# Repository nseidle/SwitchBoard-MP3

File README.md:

Switchboard MP3 Player
=======

This project documents the modifications made to a vintage phone switchboard. This is an interactive exhibit at the WOW children's museum in Lafayette. Any of the audio plugs can be inserted into any of the ports in the top console. The light will turn on and one of 74 MP3s will play out the corded phone.

It was awesome to work on.

I appreciate the switchboard contained its own solder. From 1956!

Above, shows all the original glass lamp covers

[Movie of LEDs](Images/Switchboard%20LEDs.mp4)

Repository Contents
-------------------

* **/firmware** - The code that runs on the ESP32.
* **/hardware** - A custom I/O board capable of 40 inputs and 40 outputs per board, with the ability to chain any number of boards together.

License Information
-------------------

This design is [OSHW](http://www.oshwa.org/definition/) and public domain but you buy me a beer if you use this and we meet someday ([Beerware license](http://en.wikipedia.org/wiki/Beerware)).

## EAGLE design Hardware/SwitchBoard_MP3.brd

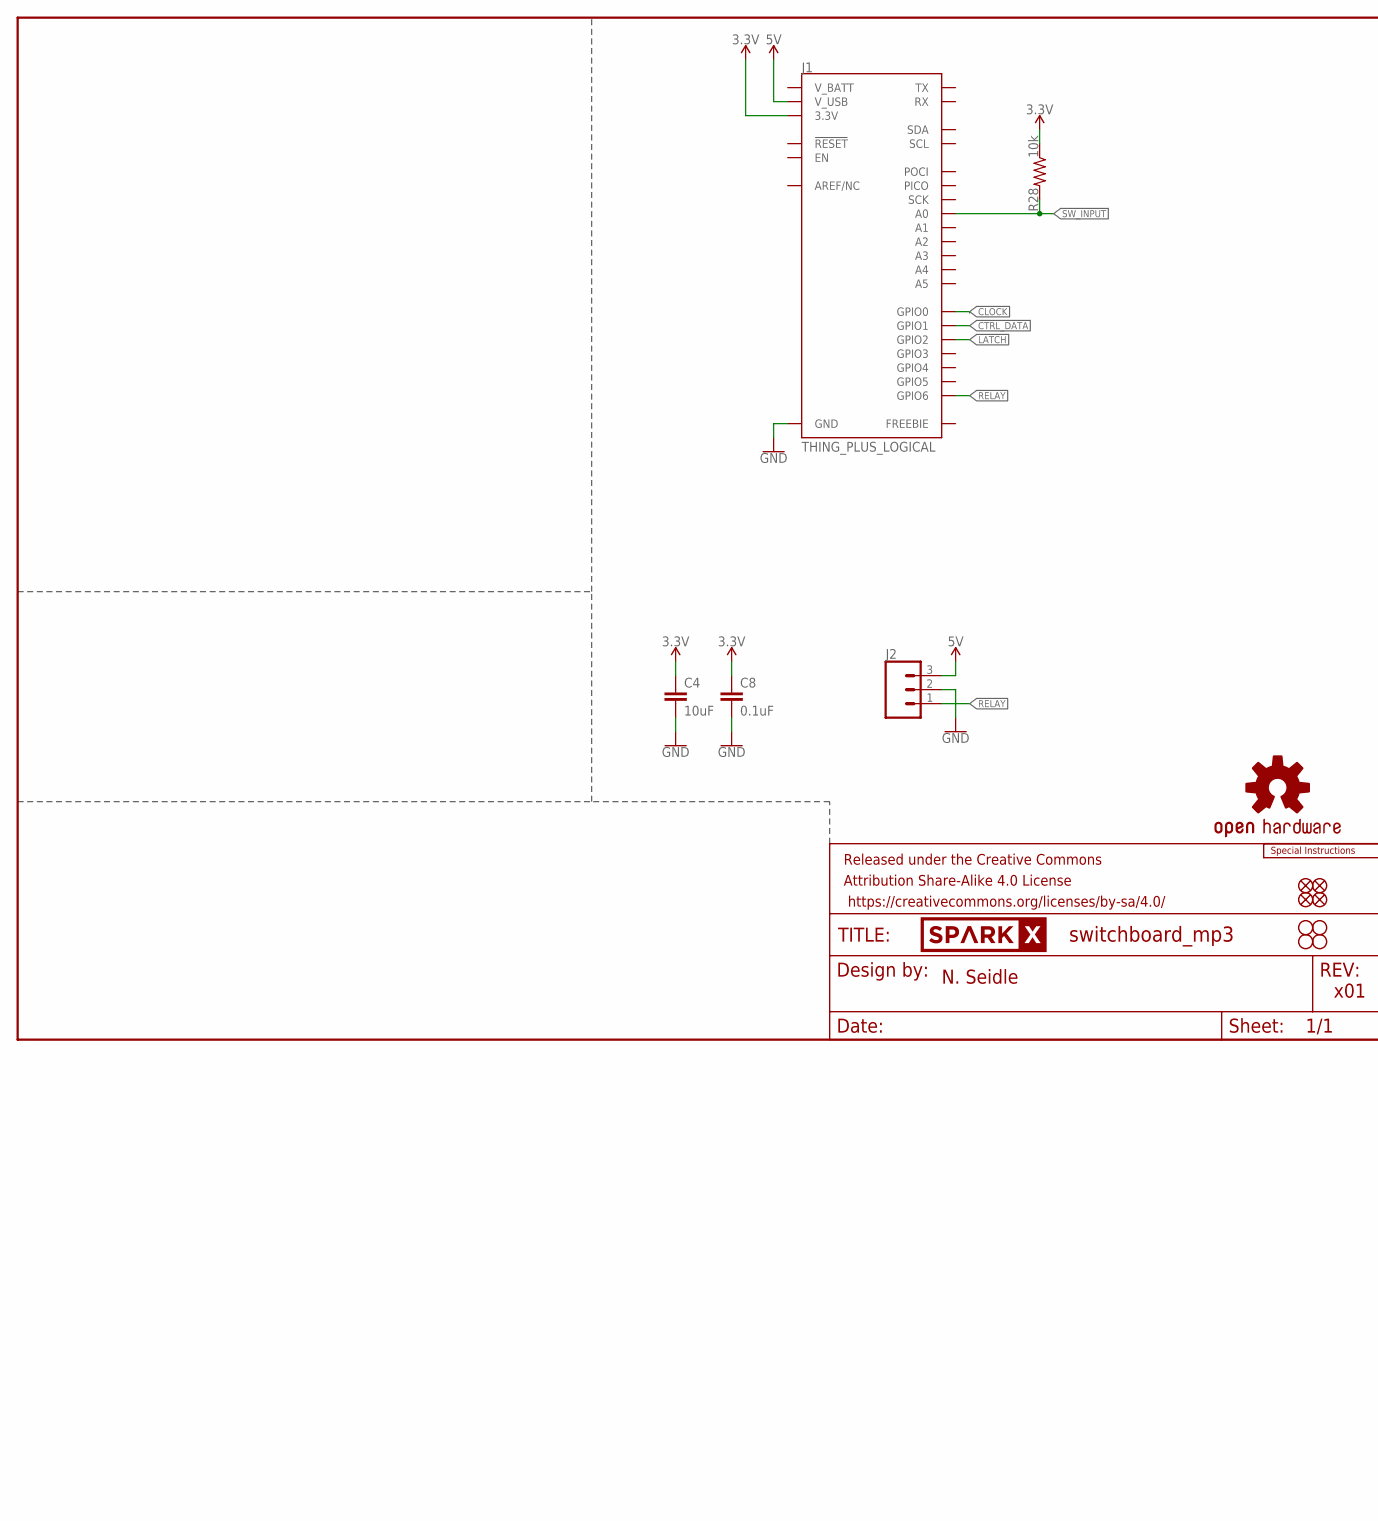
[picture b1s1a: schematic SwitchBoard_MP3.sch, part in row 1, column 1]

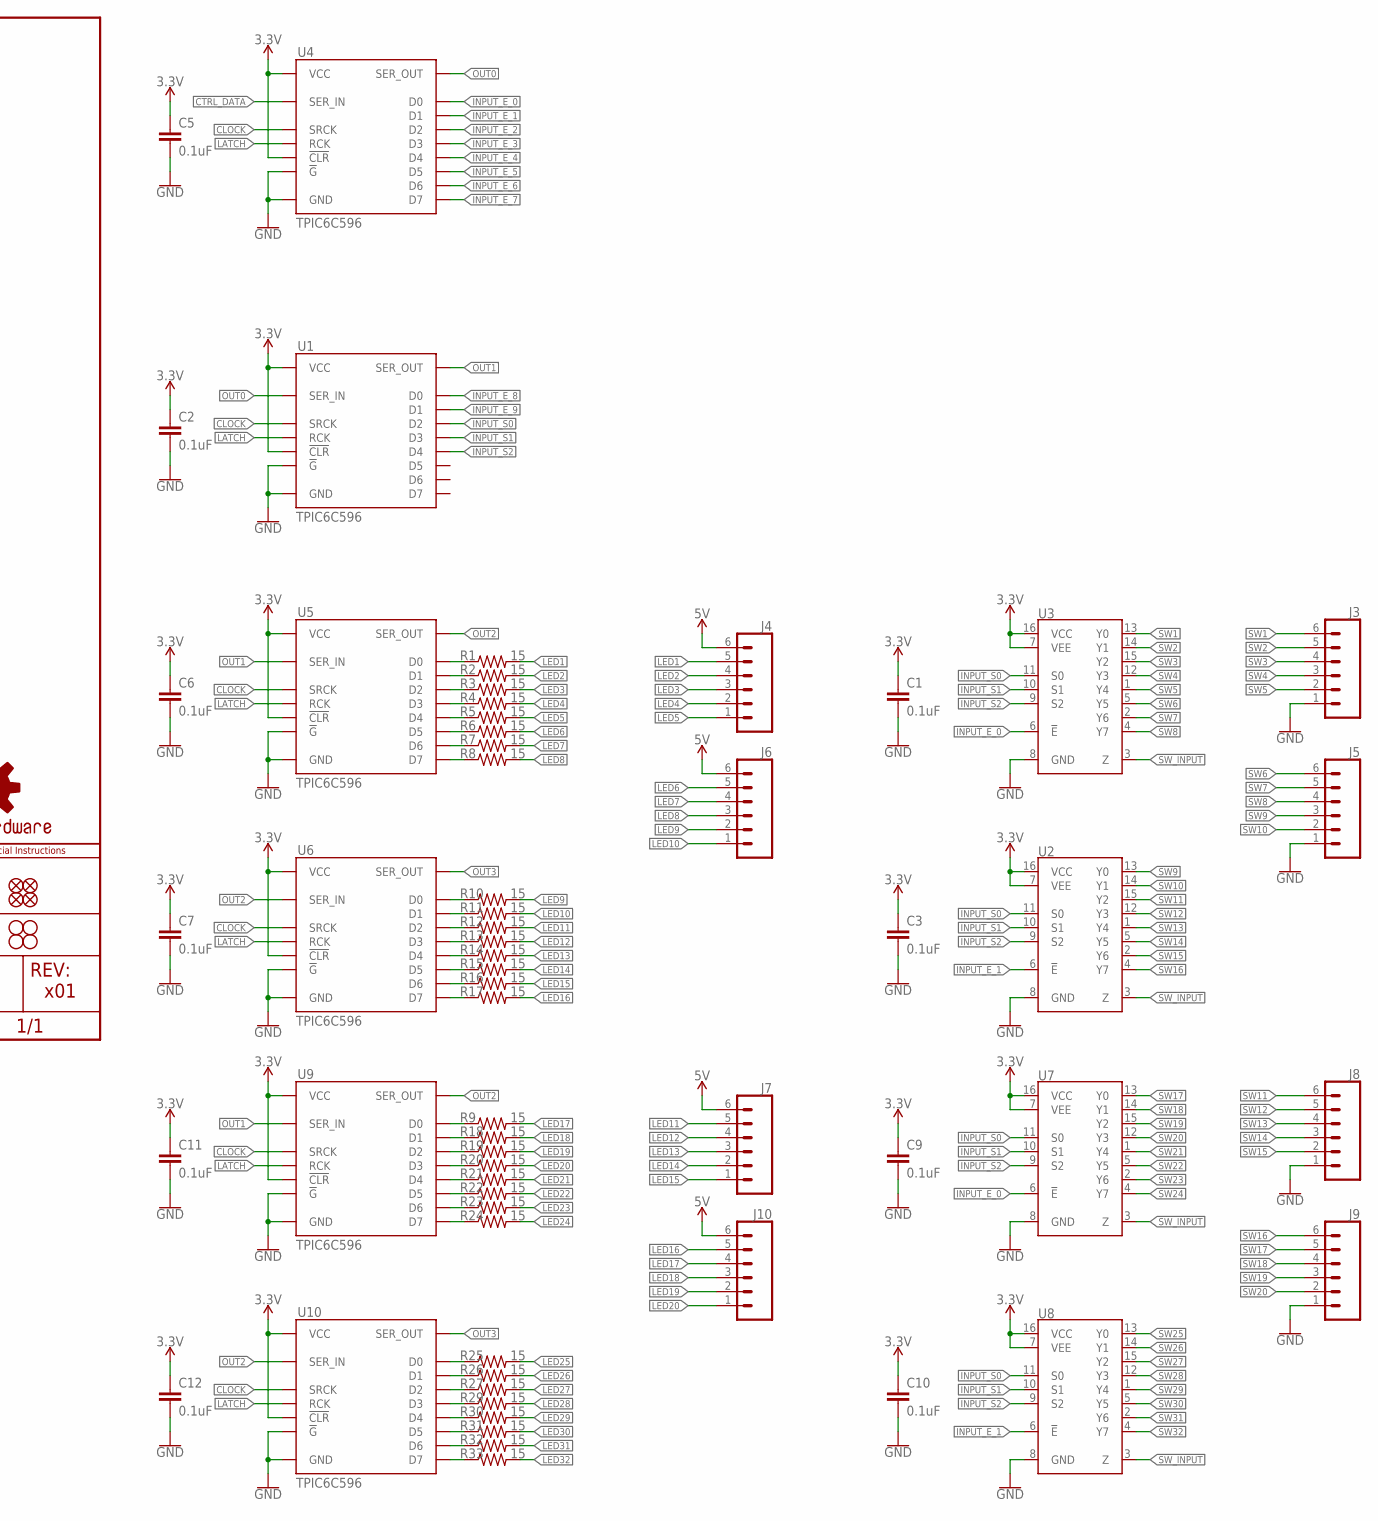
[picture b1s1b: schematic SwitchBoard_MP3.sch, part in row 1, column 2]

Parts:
C1, C2, C3, C5, C6, C7, C8, C9, C10, C11, C12: 0.1uF; 0603
C4: 10uF; 0805
FD1, FD2, FD3, FD4: FIDUCIAL1X2; FIDUCIAL-1X2
FRAME1: FRAME-LETTER; CREATIVE_COMMONS
H1, H2, H3, H4: STAND-OFF
J1: THING_PLUS_LOGICAL; THING_PLUS
J2: CONN_03JST-PTH-NS; JST-3-PTH-NS
J3, J4, J5, J6, J7, J8, J9, J10: CONN_06JST-SMD-LOCKING; JST-6-SMD-1.25MM-LOCKING
LOGO1: SPECIAL_INSTRUCTIONS-ORDERING; ORDERING_INSTRUCTIONS
LOGO2: OSHW-LOGOS; OSHW-LOGO-S
R1, R2, R3, R4, R5, R6, R7, R8, R9, R10, R11, R12, R13, R14, R15, R16, R17, R18, R19, R20, R21, R22, R23, R24, R25, R26, R27, R29, R30, R31, R32, R33: 15; 0603
R28: 10k; 0603
U1, U4, U5, U6, U9, U10: TPIC6C596; SO016
U2, U3, U7, U8: 744051; SO16
U$1: SPARKX-LOGO4; SPARKX-MEDIUM

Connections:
3.3V: C1.1, C2.1, C3.1, C4.1, C5.1, C6.1, C7.1, C8.1, C9.1, C10.1, C11.1, C12.1, J1.27 (3.3V), R28.1, U1.1 (VCC), U1.7 (!CLR), U2.7 (VEE), U2.16 (VCC), U3.7 (VEE), U3.16 (VCC), U4.1 (VCC), U4.7 (!CLR), U5.1 (VCC), U5.7 (!CLR), U6.1 (VCC), U6.7 (!CLR), U7.7 (VEE), U7.16 (VCC), U8.7 (VEE), U8.16 (VCC), U9.1 (VCC), U9.7 (!CLR), U10.1 (VCC), U10.7 (!CLR)
5V: J1.10 (V_USB), J2.3, J4.6, J6.6, J7.6, J10.6
CLOCK: J1.9 (GPIO0), U1.15 (SRCK), U4.15 (SRCK), U5.15 (SRCK), U6.15 (SRCK), U9.15 (SRCK), U10.15 (SRCK)
CTRL_DATA: J1.8 (GPIO1), U4.2 (SER_IN)
GND: C1.2, C2.2, C3.2, C4.2, C5.2, C6.2, C7.2, C8.2, C9.2, C10.2, C11.2, C12.2, J1.25 (GND), J2.2, J3.1, J5.1, J8.1, J9.1, U1.8 (!G), U1.16 (GND), U2.8 (GND), U3.8 (GND), U4.8 (!G), U4.16 (GND), U5.8 (!G), U5.16 (GND), U6.8 (!G), U6.16 (GND), U7.8 (GND), U8.8 (GND), U9.8 (!G), U9.16 (GND), U10.8 (!G), U10.16 (GND)
INPUT_!E!_0: U3.6 (!E!), U4.3 (D0), U7.6 (!E!)
INPUT_!E!_1: U2.6 (!E!), U4.4 (D1), U8.6 (!E!)
INPUT_!E!_2: U4.5 (D2)
INPUT_!E!_3: U4.6 (D3)
INPUT_!E!_4: U4.11 (D4)
INPUT_!E!_5: U4.12 (D5)
INPUT_!E!_6: U4.13 (D6)
INPUT_!E!_7: U4.14 (D7)
INPUT_!E!_8: U1.3 (D0)
INPUT_!E!_9: U1.4 (D1)
INPUT_S0: U1.5 (D2), U2.11 (S0), U3.11 (S0), U7.11 (S0), U8.11 (S0)
INPUT_S1: U1.6 (D3), U2.10 (S1), U3.10 (S1), U7.10 (S1), U8.10 (S1)
INPUT_S2: U1.11 (D4), U2.9 (S2), U3.9 (S2), U7.9 (S2), U8.9 (S2)
LATCH: J1.7 (GPIO2), U1.10 (RCK), U4.10 (RCK), U5.10 (RCK), U6.10 (RCK), U9.10 (RCK), U10.10 (RCK)
LED1: J4.5, R1.2
LED2: J4.4, R2.2
LED3: J4.3, R3.2
LED4: J4.2, R4.2
LED5: J4.1, R5.2
LED6: J6.5, R6.2
LED7: J6.4, R7.2
LED8: J6.3, R8.2
LED9: J6.2, R10.2
LED10: J6.1, R11.2
LED11: J7.5, R12.2
LED12: J7.4, R13.2
LED13: J7.3, R14.2
LED14: J7.2, R15.2
LED15: J7.1, R16.2
LED16: J10.5, R17.2
LED17: J10.4, R9.2
LED18: J10.3, R18.2
LED19: J10.2, R19.2
LED20: J10.1, R20.2
LED21: R21.2
LED22: R22.2
LED23: R23.2
LED24: R24.2
LED25: R25.2
LED26: R26.2
LED27: R27.2
LED28: R29.2
LED29: R30.2
LED30: R31.2
LED31: R32.2
LED32: R33.2
unnamed: R1.1, U5.3 (D0)
unnamed: R2.1, U5.4 (D1)
unnamed: R3.1, U5.5 (D2)
unnamed: R4.1, U5.6 (D3)
unnamed: R5.1, U5.11 (D4)
unnamed: R6.1, U5.12 (D5)
unnamed: R7.1, U5.13 (D6)
unnamed: R8.1, U5.14 (D7)
unnamed: R9.1, U9.3 (D0)
unnamed: R10.1, U6.3 (D0)
unnamed: R11.1, U6.4 (D1)
unnamed: R12.1, U6.5 (D2)
unnamed: R13.1, U6.6 (D3)
unnamed: R14.1, U6.11 (D4)
unnamed: R15.1, U6.12 (D5)
unnamed: R16.1, U6.13 (D6)
unnamed: R17.1, U6.14 (D7)
unnamed: R18.1, U9.4 (D1)
unnamed: R19.1, U9.5 (D2)
unnamed: R20.1, U9.6 (D3)
unnamed: R21.1, U9.11 (D4)
unnamed: R22.1, U9.12 (D5)
unnamed: R23.1, U9.13 (D6)
unnamed: R24.1, U9.14 (D7)
unnamed: R25.1, U10.3 (D0)
unnamed: R26.1, U10.4 (D1)
unnamed: R27.1, U10.5 (D2)
unnamed: R29.1, U10.6 (D3)
unnamed: R30.1, U10.11 (D4)
unnamed: R31.1, U10.12 (D5)
unnamed: R32.1, U10.13 (D6)
unnamed: R33.1, U10.14 (D7)
OUT0: U1.2 (SER_IN), U4.9 (SER_OUT)
OUT1: U1.9 (SER_OUT), U5.2 (SER_IN), U9.2 (SER_IN)
OUT2: U5.9 (SER_OUT), U6.2 (SER_IN), U9.9 (SER_OUT), U10.2 (SER_IN)
OUT3: U6.9 (SER_OUT), U10.9 (SER_OUT)
RELAY: J1.3 (GPIO6), J2.1
SW1: J3.6, U3.13 (Y0)
SW2: J3.5, U3.14 (Y1)
SW3: J3.4, U3.15 (Y2)
SW4: J3.3, U3.12 (Y3)
SW5: J3.2, U3.1 (Y4)
SW6: J5.6, U3.5 (Y5)
SW7: J5.5, U3.2 (Y6)
SW8: J5.4, U3.4 (Y7)
SW9: J5.3, U2.13 (Y0)
SW10: J5.2, U2.14 (Y1)
SW11: J8.6, U2.15 (Y2)
SW12: J8.5, U2.12 (Y3)
SW13: J8.4, U2.1 (Y4)
SW14: J8.3, U2.5 (Y5)
SW15: J8.2, U2.2 (Y6)
SW16: J9.6, U2.4 (Y7)
SW17: J9.5, U7.13 (Y0)
SW18: J9.4, U7.14 (Y1)
SW19: J9.3, U7.15 (Y2)
SW20: J9.2, U7.12 (Y3)
SW21: U7.1 (Y4)
SW22: U7.5 (Y5)
SW23: U7.2 (Y6)
SW24: U7.4 (Y7)
SW25: U8.13 (Y0)
SW26: U8.14 (Y1)
SW27: U8.15 (Y2)
SW28: U8.12 (Y3)
SW29: U8.1 (Y4)
SW30: U8.5 (Y5)
SW31: U8.2 (Y6)
SW32: U8.4 (Y7)
SW_INPUT: J1.24 (A0), R28.2, U2.3 (Z), U3.3 (Z), U7.3 (Z), U8.3 (Z)

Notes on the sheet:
x01
N. Seidle

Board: 4 copper layers, 88 parts (2 on the bottom side), 89 nets, no tracks yet.

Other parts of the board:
U$2: 5_4_3_2_1_V0
U$3, U$7, U$11, U$12: LAMP0
U$4, U$6, U$8, U$9, U$10: SWITCH0
U$5: G_5_4_3_2_10

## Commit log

2023-03-13 Add images
2023-03-13 Add video
2023-03-13 Remove old files
2023-03-13 Add animated gif

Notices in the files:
parts and their libraries:
SparkFun-Aesthetics: Licensing: Creative Commons ShareAlike 4.0 International - https://creativecommons.org/licenses/by-sa/4.0
SparkFun-Aesthetics: Released under the Creative Commons Attribution Share-Alike 4.0 License
SparkFun-Aesthetics: https://creativecommons.org/licenses/by-sa/4.0
